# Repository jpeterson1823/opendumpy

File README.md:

# OpenDumpy: GB/C Dumping Tool

OpenDumpy is an open-source Gameboy and Gameboy Color cartridge dumper.

Planned Features:
- LCD Display Screen
- MicroSD Card Support
- Capacitive Touch Controls
- ROM Dump
  - Save direct to computer over USB via use of software
  - Save to MicroSD card through on-board UI
- SRAM Dump
  - Save direct to computer over USB via use of software
  - Save to MicroSD card through on-board UI
- SRAM Uploading from file
  - Direct from computer over USB via use of software
  - Load from MicroSD card through on-board UI
- Lots of docs!

Future versions of OpenDumpy will have a modular cartridge port to support NES, SNES, N64, as well as GB(A) games.

## Current Fabrication Status Status

OpenDumpy v3 has finished design and is being checked thoroughly for any design errors.
Ordering of components and PCBs will be completed early September 2026.

OpenDumpy v3 will include development pinouts accessible via IDC connectors on the right side of the board in the event of an uncaught error in PCB/Schematic design. This will allow for the continued development of firmware without needing to have a fixed board this time around.

## Setup & Building the UF2

### Install Required Packages

For Arch Linux:
- `cmake`
- `python`
- `base-devel`
- `arm-none-eabi-gcc`
- `arm-none-eabi-newlib`
- `arm-none-eabi-binutils`

For apt-based systems:
- `cmake`
- `python3`
- `build-essential`
- `gcc-arm-none-eabi`
- `libnewlib-arm-none-eabi`
- `libstdc++-arm-none-eabi-newlib`

### Cloning the Repo

When cloning this repo, make sure to _recursively_ initialize all submodules:

```
git clone https://github.com/jpeterson1823/opendumpy.git
cd opendumpy
git submodule update --init --recursive
```

### Compiling the Firmware

Assuming all package dependencies have been installed, building should be completed with CMake and Make.

It is recommended to create a build folder as to not muddy up the file tree:

```
mkdir firmware/build
cd firmware/build
cmake ..
make -j4
```

### Uploading the Firmware

Press the BOOTSEL button on OpenDumpy, then plug into USB port of machine. It will mount as a USB drive. Upload the built `opendumpy.uf2` file to the mounted drive. Voila!

## Images

### OpenDumpy v3
<div>

</div>

### OpenDumpy v1-2
<div>

</div>

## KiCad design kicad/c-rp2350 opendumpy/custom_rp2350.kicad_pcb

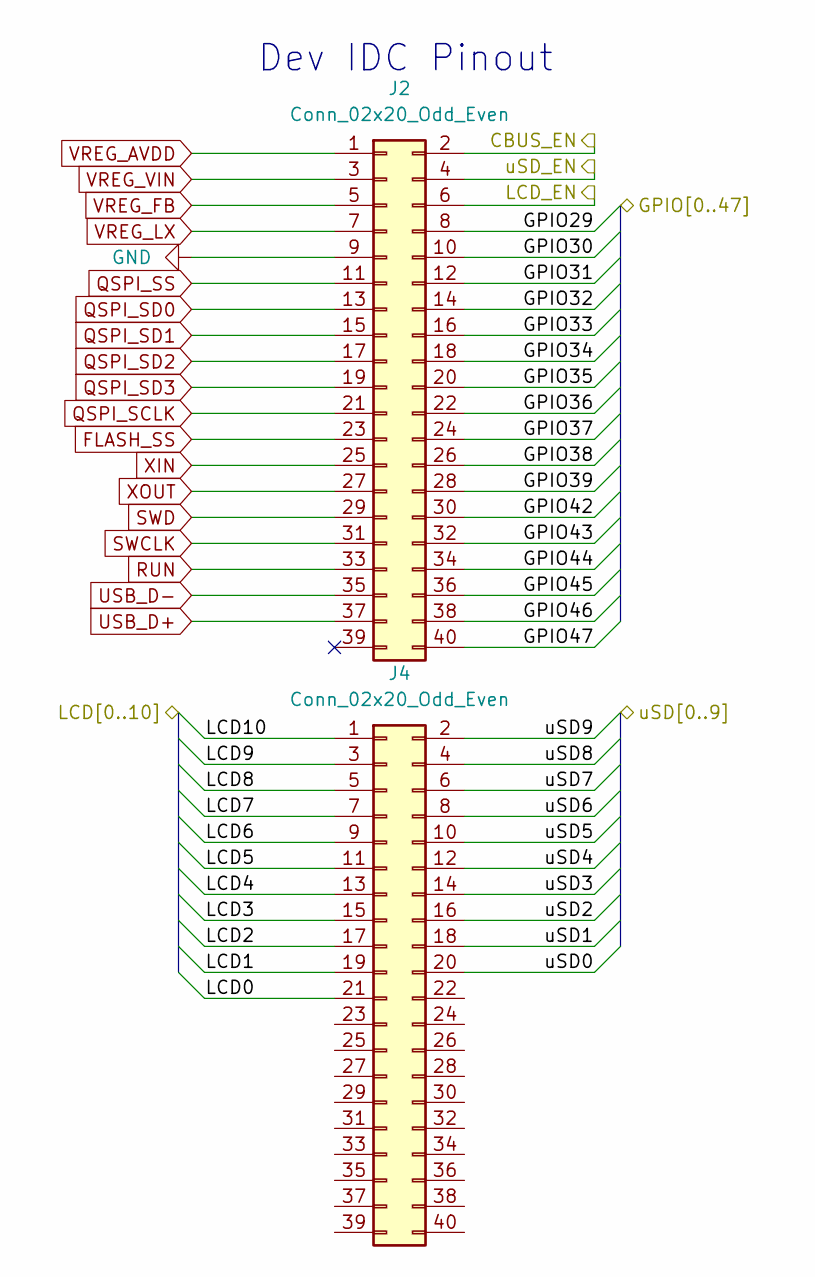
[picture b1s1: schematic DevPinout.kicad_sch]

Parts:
J2, J4: Conn_02x20_Odd_Even; Molex_8783240xx_2x20_P2.0mm_Header_Vertical_Polarized

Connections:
/DevPinout/CBUS_EN: J2.2; also elsewhere on the board
/DevPinout/LCD0: J4.21; also elsewhere on the board
/DevPinout/LCD1: J4.19; also elsewhere on the board
/DevPinout/LCD2: J4.17; also elsewhere on the board
/DevPinout/LCD3: J4.15; also elsewhere on the board
/DevPinout/LCD4: J4.13; also elsewhere on the board
/DevPinout/LCD5: J4.11; also elsewhere on the board
/DevPinout/LCD6: J4.9; also elsewhere on the board
/DevPinout/LCD7: J4.7; also elsewhere on the board
/DevPinout/LCD8: J4.5; also elsewhere on the board
/DevPinout/LCD9: J4.3; also elsewhere on the board
/DevPinout/LCD10: J4.1; also elsewhere on the board
/DevPinout/LCD_EN: J2.6; also elsewhere on the board
/DevPinout/uSD0: J4.20; also elsewhere on the board
/DevPinout/uSD1: J4.18; also elsewhere on the board
/DevPinout/uSD2: J4.16; also elsewhere on the board
/DevPinout/uSD3: J4.14; also elsewhere on the board
/DevPinout/uSD4: J4.12; also elsewhere on the board
/DevPinout/uSD5: J4.10; also elsewhere on the board
/DevPinout/uSD6: J4.8; also elsewhere on the board
/DevPinout/uSD7: J4.6; also elsewhere on the board
/DevPinout/uSD8: J4.4; also elsewhere on the board
/DevPinout/uSD9: J4.2; also elsewhere on the board
/DevPinout/uSD_EN: J2.4; also elsewhere on the board
/GPIO29: J2.8; also elsewhere on the board
/GPIO30: J2.10; also elsewhere on the board
/GPIO31: J2.12; also elsewhere on the board
/GPIO32: J2.14; also elsewhere on the board
/GPIO33: J2.16; also elsewhere on the board
/GPIO34: J2.18; also elsewhere on the board
/GPIO35: J2.20; also elsewhere on the board
/GPIO36: J2.22; also elsewhere on the board
/GPIO37: J2.24; also elsewhere on the board
/GPIO38: J2.26; also elsewhere on the board
/GPIO39: J2.28; also elsewhere on the board
/GPIO42: J2.30; also elsewhere on the board
/GPIO43: J2.32; also elsewhere on the board
/GPIO44: J2.34; also elsewhere on the board
/GPIO45: J2.36; also elsewhere on the board
/GPIO46: J2.38; also elsewhere on the board
/GPIO47: J2.40; also elsewhere on the board
FLASH_SS: J2.23; also elsewhere on the board
GND: J2.9; also elsewhere on the board
QSPI_SCLK: J2.21; also elsewhere on the board
QSPI_SD0: J2.13; also elsewhere on the board
QSPI_SD1: J2.15; also elsewhere on the board
QSPI_SD2: J2.17; also elsewhere on the board
QSPI_SD3: J2.19; also elsewhere on the board
QSPI_SS: J2.11; also elsewhere on the board
RUN: J2.33; also elsewhere on the board
SWCLK: J2.31; also elsewhere on the board
SWD: J2.29; also elsewhere on the board
USB_D+: J2.37; also elsewhere on the board
USB_D-: J2.35; also elsewhere on the board
VREG_AVDD: J2.1; also elsewhere on the board
VREG_FB: J2.5; also elsewhere on the board
VREG_LX: J2.7; also elsewhere on the board
VREG_VIN: J2.3; also elsewhere on the board
XIN: J2.25; also elsewhere on the board
XOUT: J2.27; also elsewhere on the board

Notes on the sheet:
Dev IDC Pinout

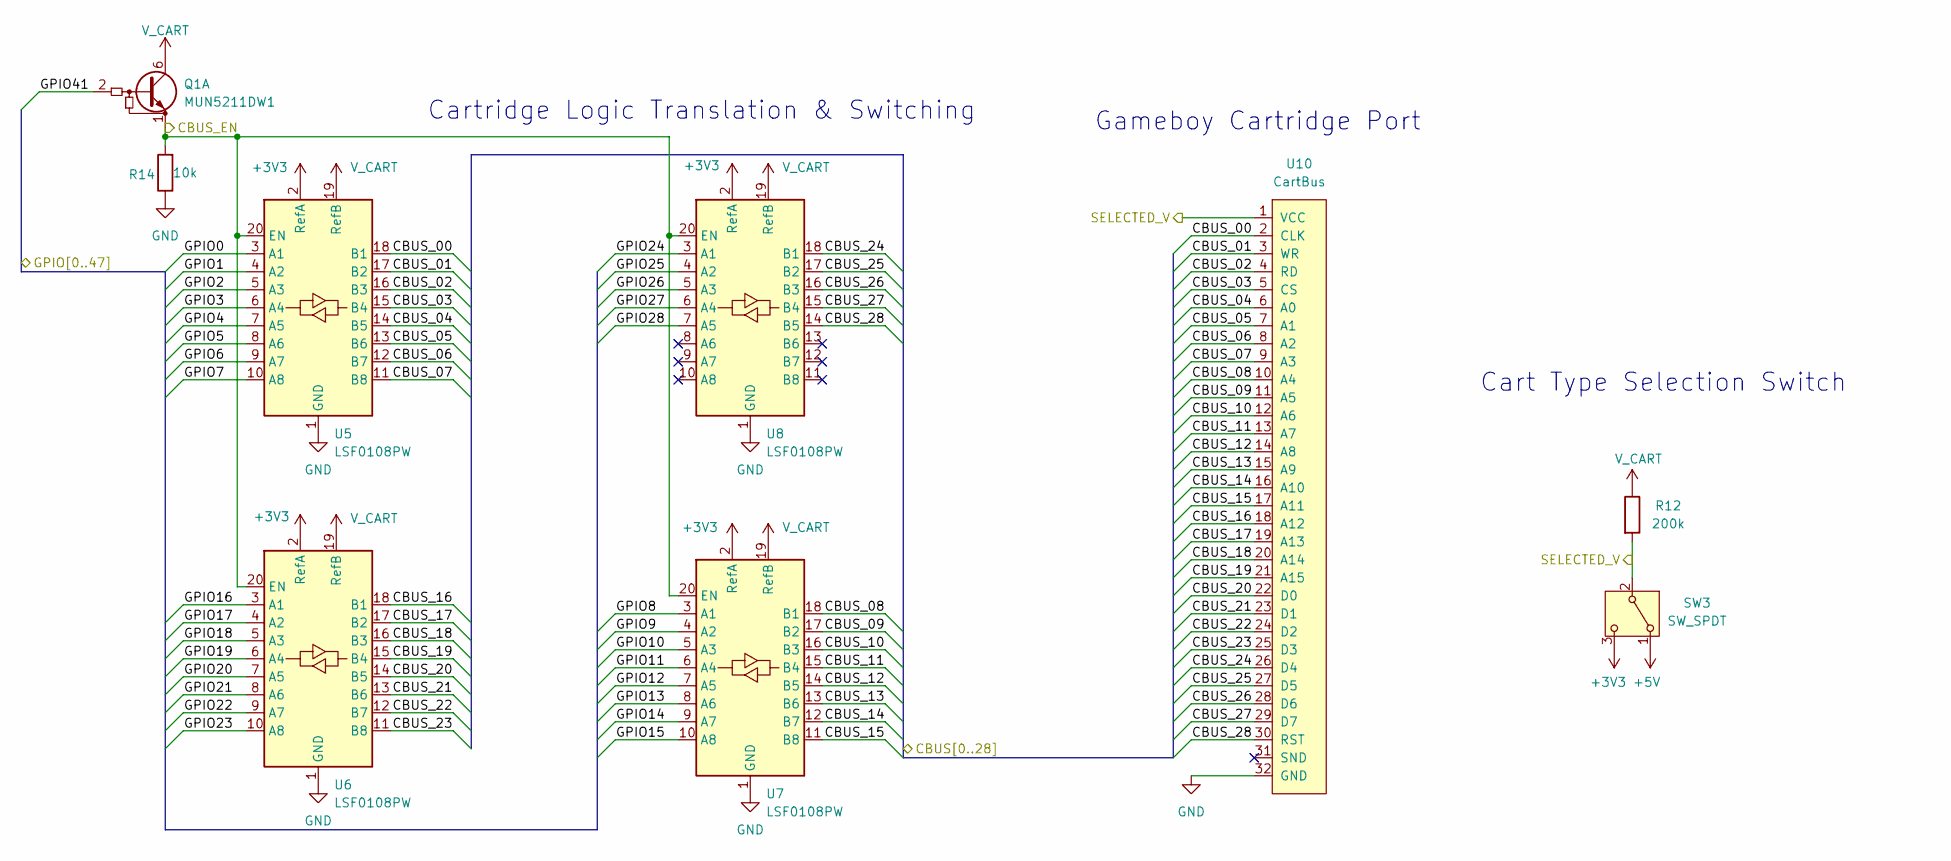
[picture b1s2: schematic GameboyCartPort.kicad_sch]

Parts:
Q1: MUN5211DW1; SOT-363_SC-70-6
R12: 200k; R_01005_0402Metric
R14: 10k; R_0402_1005Metric_Pad0.72x0.64mm_HandSolder
SW3: SW_SPDT; CL-SB-12B-01_NDC
U5, U6, U7, U8: LSF0108PW; TSSOP-20_4.4x6.5mm_P0.65mm
U10: CartBus; DSL_Cartridge_Reader

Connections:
+5V: SW3.1 (A); also elsewhere on the board
/DevPinout/CBUS_EN: Q1.1 (E1), R14.2, U5.20 (EN), U6.20 (EN), U7.20 (EN), U8.20 (EN); also elsewhere on the board
/GPIO0: U5.3 (A1); also elsewhere on the board
/GPIO1: U5.4 (A2); also elsewhere on the board
/GPIO2: U5.5 (A3); also elsewhere on the board
/GPIO3: U5.6 (A4); also elsewhere on the board
/GPIO4: U5.7 (A5); also elsewhere on the board
/GPIO5: U5.8 (A6); also elsewhere on the board
/GPIO6: U5.9 (A7); also elsewhere on the board
/GPIO7: U5.10 (A8); also elsewhere on the board
/GPIO8: U7.3 (A1); also elsewhere on the board
/GPIO9: U7.4 (A2); also elsewhere on the board
/GPIO10: U7.5 (A3); also elsewhere on the board
/GPIO11: U7.6 (A4); also elsewhere on the board
/GPIO12: U7.7 (A5); also elsewhere on the board
/GPIO13: U7.8 (A6); also elsewhere on the board
/GPIO14: U7.9 (A7); also elsewhere on the board
/GPIO15: U7.10 (A8); also elsewhere on the board
/GPIO16: U6.3 (A1); also elsewhere on the board
/GPIO17: U6.4 (A2); also elsewhere on the board
/GPIO18: U6.5 (A3); also elsewhere on the board
/GPIO19: U6.6 (A4); also elsewhere on the board
/GPIO20: U6.7 (A5); also elsewhere on the board
/GPIO21: U6.8 (A6); also elsewhere on the board
/GPIO22: U6.9 (A7); also elsewhere on the board
/GPIO23: U6.10 (A8); also elsewhere on the board
/GPIO24: U8.3 (A1); also elsewhere on the board
/GPIO25: U8.4 (A2); also elsewhere on the board
/GPIO26: U8.5 (A3); also elsewhere on the board
/GPIO27: U8.6 (A4); also elsewhere on the board
/GPIO28: U8.7 (A5); also elsewhere on the board
/GPIO41: Q1.2 (B1); also elsewhere on the board
/GameboyCartPort/CBUS_00: U5.18 (B1), U10.2 (CLK~)
/GameboyCartPort/CBUS_01: U5.17 (B2), U10.3 (WR)
/GameboyCartPort/CBUS_02: U5.16 (B3), U10.4 (RD)
/GameboyCartPort/CBUS_03: U5.15 (B4), U10.5 (CS)
/GameboyCartPort/CBUS_04: U5.14 (B5), U10.6 (A0)
/GameboyCartPort/CBUS_05: U5.13 (B6), U10.7 (A1)
/GameboyCartPort/CBUS_06: U5.12 (B7), U10.8 (A2)
/GameboyCartPort/CBUS_07: U5.11 (B8), U10.9 (A3)
/GameboyCartPort/CBUS_08: U7.18 (B1), U10.10 (A4)
/GameboyCartPort/CBUS_09: U7.17 (B2), U10.11 (A5)
/GameboyCartPort/CBUS_10: U7.16 (B3), U10.12 (A6)
/GameboyCartPort/CBUS_11: U7.15 (B4), U10.13 (A7)
/GameboyCartPort/CBUS_12: U7.14 (B5), U10.14 (A8)
/GameboyCartPort/CBUS_13: U7.13 (B6), U10.15 (A9)
/GameboyCartPort/CBUS_14: U7.12 (B7), U10.16 (A10)
/GameboyCartPort/CBUS_15: U7.11 (B8), U10.17 (A11)
/GameboyCartPort/CBUS_16: U6.18 (B1), U10.18 (A12)
/GameboyCartPort/CBUS_17: U6.17 (B2), U10.19 (A13)
/GameboyCartPort/CBUS_18: U6.16 (B3), U10.20 (A14)
/GameboyCartPort/CBUS_19: U6.15 (B4), U10.21 (A15)
/GameboyCartPort/CBUS_20: U6.14 (B5), U10.22 (D0)
/GameboyCartPort/CBUS_21: U6.13 (B6), U10.23 (D1)
/GameboyCartPort/CBUS_22: U6.12 (B7), U10.24 (D2)
/GameboyCartPort/CBUS_23: U6.11 (B8), U10.25 (D3)
/GameboyCartPort/CBUS_24: U8.18 (B1), U10.26 (D4)
/GameboyCartPort/CBUS_25: U8.17 (B2), U10.27 (D5)
/GameboyCartPort/CBUS_26: U8.16 (B3), U10.28 (D6)
/GameboyCartPort/CBUS_27: U8.15 (B4), U10.29 (D7)
/GameboyCartPort/CBUS_28: U8.14 (B5), U10.30 (RST)
/GameboyCartPort/SELECTED_V: R12.2, SW3.2 (B), U10.1 (VCC)
GND: R14.1, U5.1 (GND), U6.1 (GND), U7.1 (GND), U8.1 (GND), U10.32 (GND); also elsewhere on the board
VREG_VIN: SW3.3 (C), U5.2 (RefA), U6.2 (RefA), U7.2 (RefA), U8.2 (RefA); also elsewhere on the board
V_CART: Q1.6 (C1), R12.1, U5.19 (RefB), U6.19 (RefB), U7.19 (RefB), U8.19 (RefB)

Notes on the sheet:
Cartridge Logic Translation & Switching
Cart Type Selection Switch
Gameboy Cartridge Port

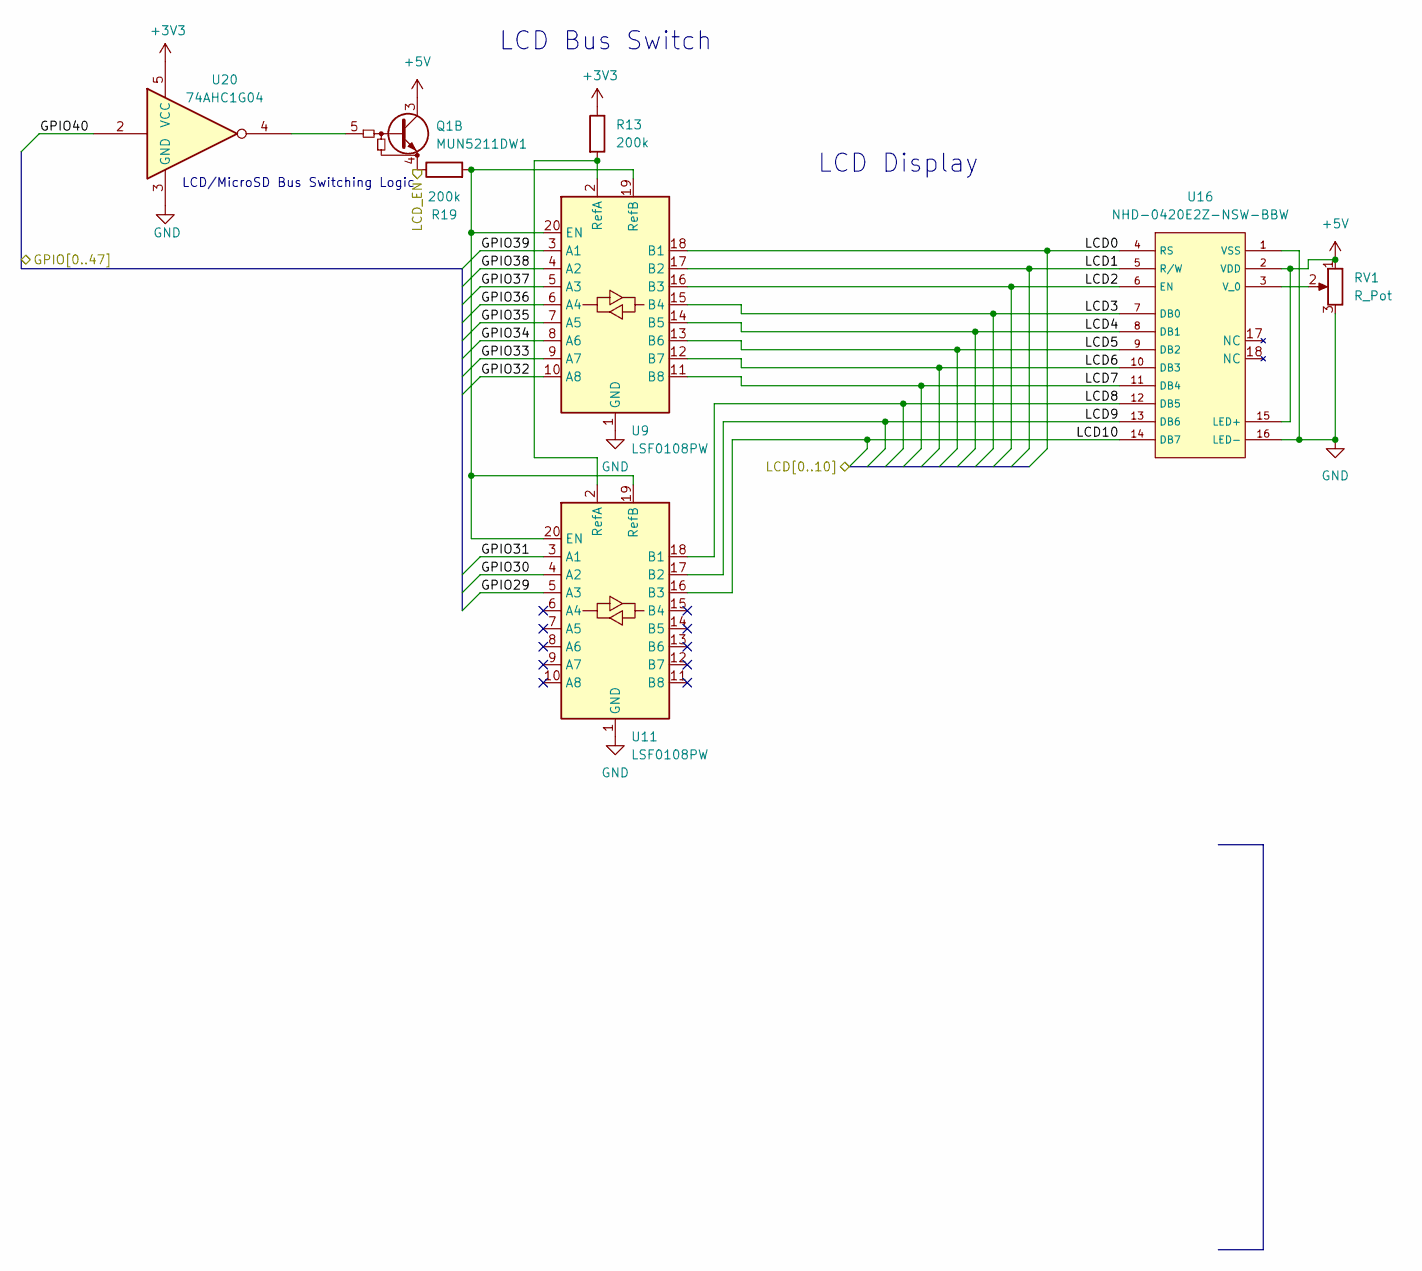
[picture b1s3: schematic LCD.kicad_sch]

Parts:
Q1: MUN5211DW1; SOT-363_SC-70-6
R13, R19: 200k; R_01005_0402Metric
RV1: R_Pot; Potentiometer_Bourns_TC33X_Vertical
U9, U11: LSF0108PW; TSSOP-20_4.4x6.5mm_P0.65mm
U16: NHD-0420E2Z-NSW-BBW
U20: 74AHC1G04; SOT-353_SC-70-5

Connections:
+5V: Q1.3 (C2), RV1.1, U16.2 (VDD), U16.15 (LED+); also elsewhere on the board
/DevPinout/LCD0: U9.18 (B1), U16.4 (RS); also elsewhere on the board
/DevPinout/LCD1: U9.17 (B2), U16.5 (R/W); also elsewhere on the board
/DevPinout/LCD2: U9.16 (B3), U16.6 (EN); also elsewhere on the board
/DevPinout/LCD3: U9.15 (B4), U16.7 (DB0); also elsewhere on the board
/DevPinout/LCD4: U9.14 (B5), U16.8 (DB1); also elsewhere on the board
/DevPinout/LCD5: U9.13 (B6), U16.9 (DB2); also elsewhere on the board
/DevPinout/LCD6: U9.12 (B7), U16.10 (DB3); also elsewhere on the board
/DevPinout/LCD7: U9.11 (B8), U16.11 (DB4); also elsewhere on the board
/DevPinout/LCD8: U11.18 (B1), U16.12 (DB5); also elsewhere on the board
/DevPinout/LCD9: U11.17 (B2), U16.13 (DB6); also elsewhere on the board
/DevPinout/LCD10: U11.16 (B3), U16.14 (DB7); also elsewhere on the board
/DevPinout/LCD_EN: Q1.4 (E2), R19.1; also elsewhere on the board
/GPIO29: U11.5 (A3); also elsewhere on the board
/GPIO30: U11.4 (A2); also elsewhere on the board
/GPIO31: U11.3 (A1); also elsewhere on the board
/GPIO32: U9.10 (A8); also elsewhere on the board
/GPIO33: U9.9 (A7); also elsewhere on the board
/GPIO34: U9.8 (A6); also elsewhere on the board
/GPIO35: U9.7 (A5); also elsewhere on the board
/GPIO36: U9.6 (A4); also elsewhere on the board
/GPIO37: U9.5 (A3); also elsewhere on the board
/GPIO38: U9.4 (A2); also elsewhere on the board
/GPIO39: U9.3 (A1); also elsewhere on the board
/GPIO40: U20.2; also elsewhere on the board
GND: RV1.3, U9.1 (GND), U11.1 (GND), U16.1 (VSS), U16.16 (LED-), U20.3 (GND); also elsewhere on the board
unnamed: Q1.5 (B2), U20.4
unnamed: R19.2, U9.19 (RefB), U9.20 (EN), U11.19 (RefB), U11.20 (EN)
unnamed: R13.2, U9.2 (RefA), U11.2 (RefA)
unnamed: RV1.2, U16.3 (V_0)
VREG_VIN: R13.1, U20.5 (VCC); also elsewhere on the board

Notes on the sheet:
LCD/MicroSD Bus Switching Logic
LCD Display
LCD Bus Switch

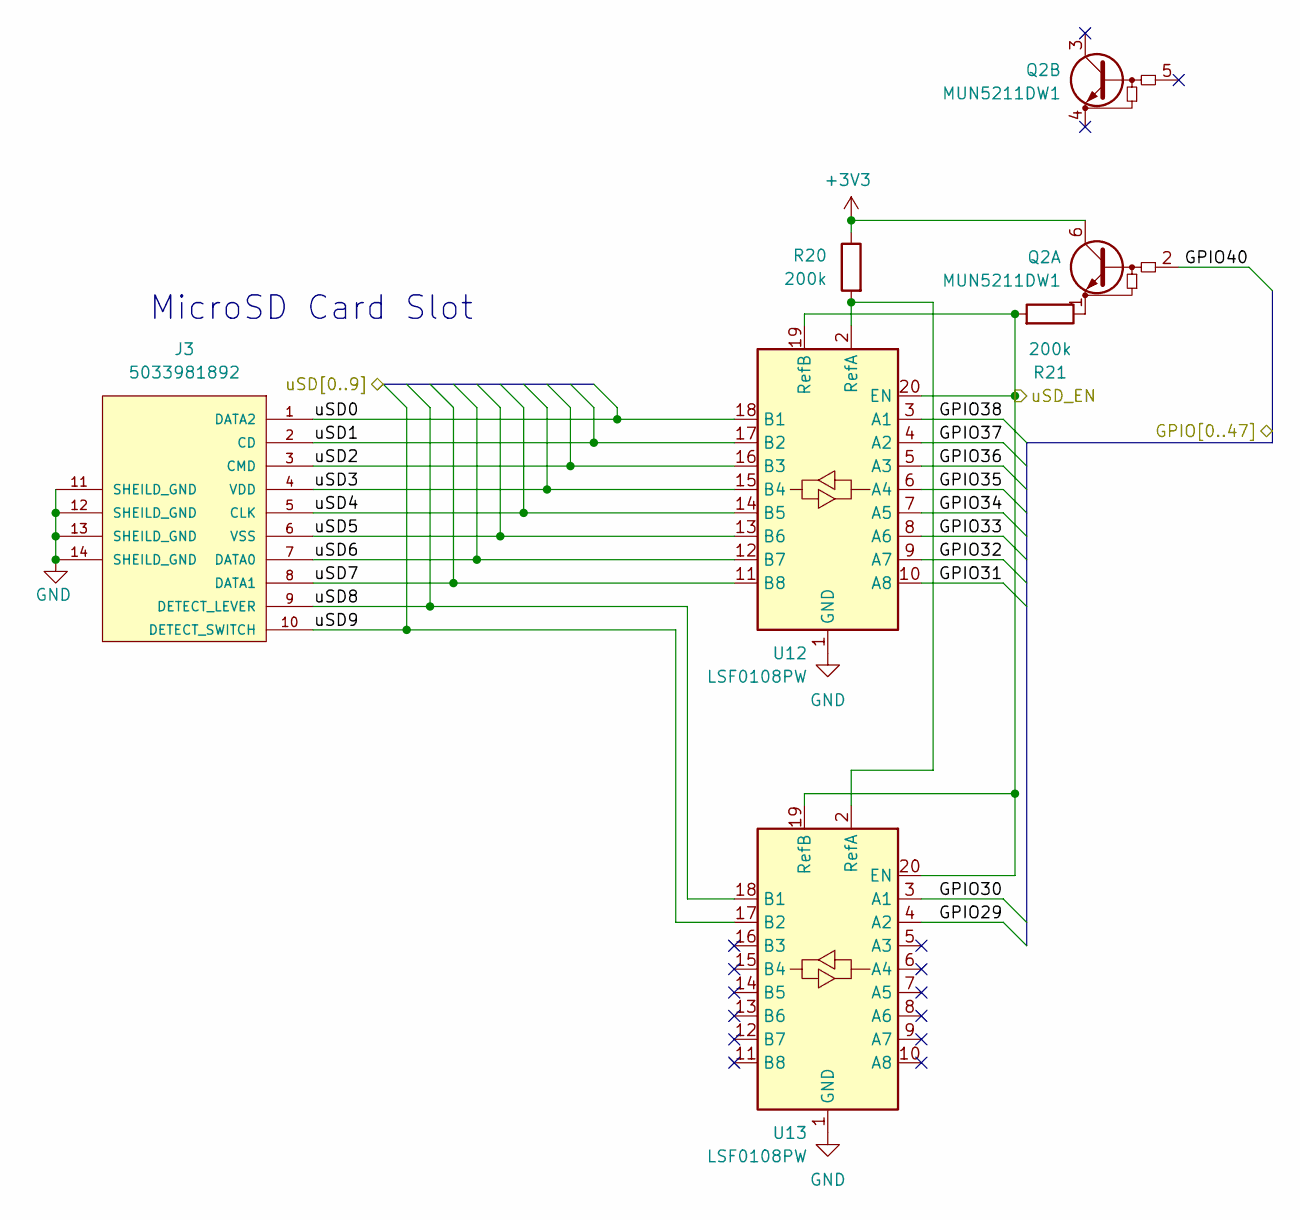
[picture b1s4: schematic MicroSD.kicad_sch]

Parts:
J3: 5033981892; CONN_503398-1892_MOL; MANUFACTURER_PART_NUMBER 5033981892; DigiKey_Part_Number WM11190CT-ND
Q2: MUN5211DW1; SOT-363_SC-70-6
R20, R21: 200k; R_01005_0402Metric
U12, U13: LSF0108PW; TSSOP-20_4.4x6.5mm_P0.65mm

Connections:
/DevPinout/uSD0: J3.1 (DATA2), U12.18 (B1); also elsewhere on the board
/DevPinout/uSD1: J3.2 (CD), U12.17 (B2); also elsewhere on the board
/DevPinout/uSD2: J3.3 (CMD), U12.16 (B3); also elsewhere on the board
/DevPinout/uSD3: J3.4 (VDD), U12.15 (B4); also elsewhere on the board
/DevPinout/uSD4: J3.5 (CLK), U12.14 (B5); also elsewhere on the board
/DevPinout/uSD5: J3.6 (VSS), U12.13 (B6); also elsewhere on the board
/DevPinout/uSD6: J3.7 (DATA0), U12.12 (B7); also elsewhere on the board
/DevPinout/uSD7: J3.8 (DATA1), U12.11 (B8); also elsewhere on the board
/DevPinout/uSD8: J3.9 (DETECT_LEVER), U13.18 (B1); also elsewhere on the board
/DevPinout/uSD9: J3.10 (DETECT_SWITCH), U13.17 (B2); also elsewhere on the board
/DevPinout/uSD_EN: R21.2, U12.19 (RefB), U12.20 (EN), U13.19 (RefB), U13.20 (EN); also elsewhere on the board
/GPIO29: U13.4 (A2); also elsewhere on the board
/GPIO30: U13.3 (A1); also elsewhere on the board
/GPIO31: U12.10 (A8); also elsewhere on the board
/GPIO32: U12.9 (A7); also elsewhere on the board
/GPIO33: U12.8 (A6); also elsewhere on the board
/GPIO34: U12.7 (A5); also elsewhere on the board
/GPIO35: U12.6 (A4); also elsewhere on the board
/GPIO36: U12.5 (A3); also elsewhere on the board
/GPIO37: U12.4 (A2); also elsewhere on the board
/GPIO38: U12.3 (A1); also elsewhere on the board
/GPIO40: Q2.2 (B1); also elsewhere on the board
GND: J3.11 (SHEILD_GND), J3.12 (SHEILD_GND), J3.13 (SHEILD_GND), J3.14 (SHEILD_GND), U12.1 (GND), U13.1 (GND); also elsewhere on the board
unnamed: Q2.1 (E1), R21.1
unnamed: R20.2, U12.2 (RefA), U13.2 (RefA)
VREG_VIN: Q2.6 (C1), R20.1; also elsewhere on the board

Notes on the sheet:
MicroSD Card Slot

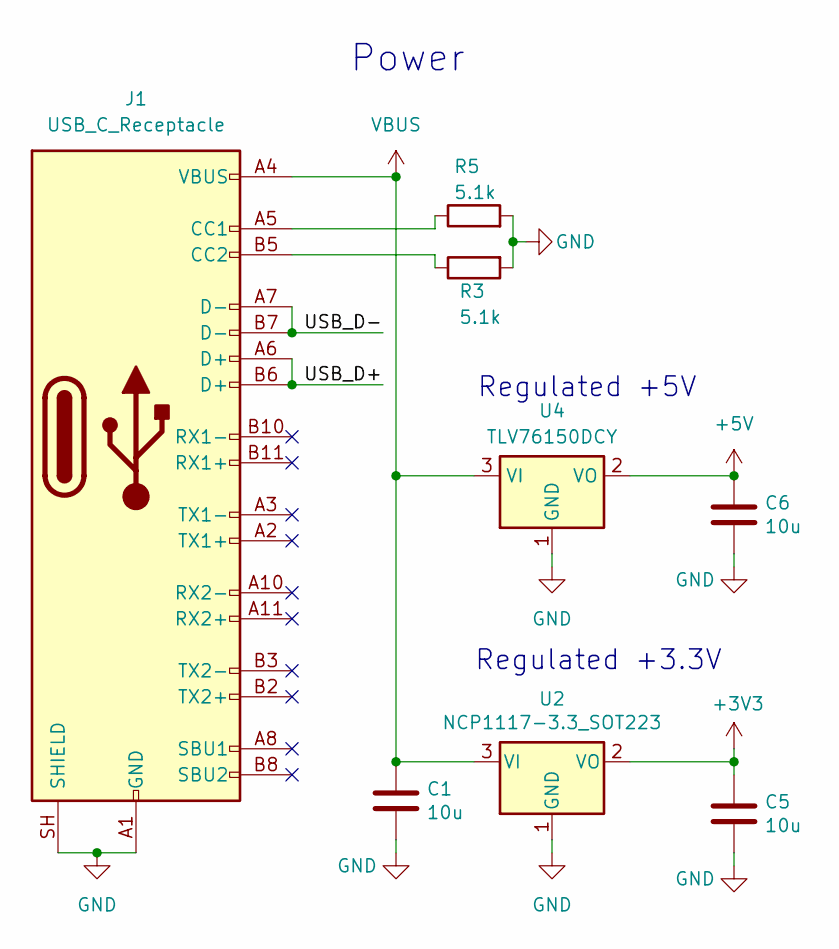
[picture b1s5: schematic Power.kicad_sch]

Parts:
C1, C5, C6: 10u; C_0402_1005Metric
J1: USB_C_Receptacle; USB_C_Receptacle_Amphenol_12401610E4-2A
R3, R5: 5.1k; R_0402_1005Metric
U2: NCP1117-3.3_SOT223; SOT-223-3_TabPin2
U4: TLV76150DCY; SOT-223-3_TabPin2

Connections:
+5V: C6.1, U4.2 (VO); also elsewhere on the board
GND: C1.2, C5.2, C6.2, J1.A1 (GND), J1.A12 (GND), J1.B1 (GND), J1.B12 (GND), J1.SH (SHIELD), R3.2, R5.2, U2.1 (GND), U4.1 (GND); also elsewhere on the board
unnamed: J1.A5 (CC1), R5.1
unnamed: J1.B5 (CC2), R3.1
USB_D+: J1.A6 (D+), J1.B6 (D+); also elsewhere on the board
USB_D-: J1.A7 (D-), J1.B7 (D-); also elsewhere on the board
VBUS: C1.1, J1.A4 (VBUS), J1.A9 (VBUS), J1.B4 (VBUS), J1.B9 (VBUS), U2.3 (VI), U4.3 (VI)
VREG_VIN: C5.1, U2.2 (VO); also elsewhere on the board

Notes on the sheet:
Power
Regulated +3.3V
Regulated +5V

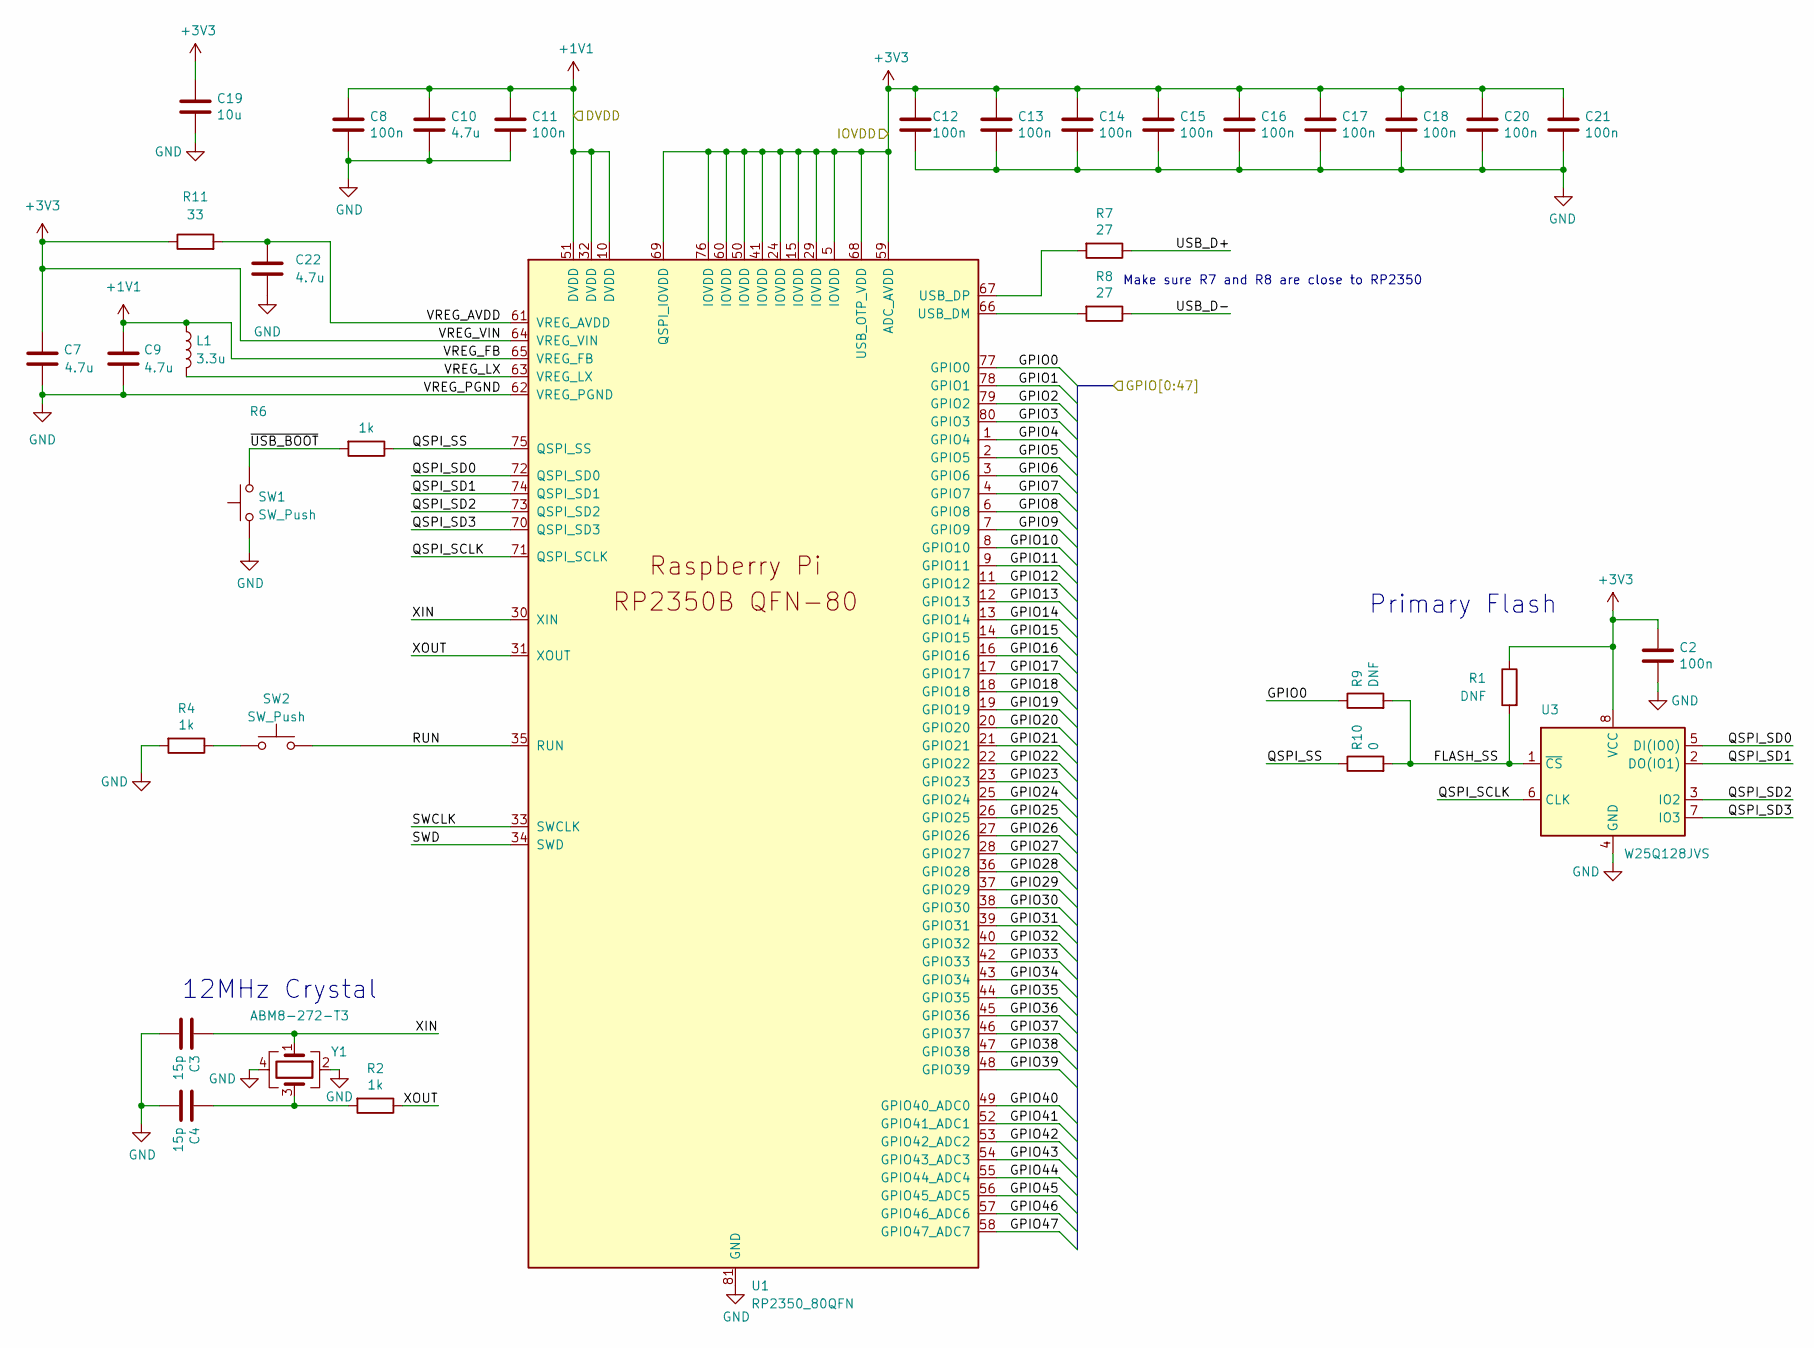
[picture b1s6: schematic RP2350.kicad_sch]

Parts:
C2, C8, C11, C12, C13, C14, C15, C16, C17, C18, C20, C21: 100n; C_0402_1005Metric
C3, C4: 15p; C_0402_1005Metric
C7, C9, C10, C22: 4.7u; C_0402_1005Metric
C19: 10u; C_0402_1005Metric
L1: 3.3u; L_01005_0402Metric
R1, R9: DNF; R_0402_1005Metric
R2, R4, R6: 1k; R_0402_1005Metric
R7, R8: 27; R_0402_1005Metric
R10: 0; R_0402_1005Metric
R11: 33; R_0402_1005Metric
SW1, SW2: SW_Push; SW_Push_1P1T_NO_Vertical_Wuerth_434133025816
U1: RP2350_80QFN; QFN-80-1EP_10x10mm_P0.4mm_EP3.4x3.4mm
U3: W25Q128JVS; SOIC-8_5.3x5.3mm_P1.27mm
Y1: ABM8-272-T3; Crystal_SMD_3225-4Pin_3.2x2.5mm

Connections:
/GPIO0: R9.1, U1.77 (GPIO0); also elsewhere on the board
/GPIO1: U1.78 (GPIO1); also elsewhere on the board
/GPIO2: U1.79 (GPIO2); also elsewhere on the board
/GPIO3: U1.80 (GPIO3); also elsewhere on the board
/GPIO4: U1.1 (GPIO4); also elsewhere on the board
/GPIO5: U1.2 (GPIO5); also elsewhere on the board
/GPIO6: U1.3 (GPIO6); also elsewhere on the board
/GPIO7: U1.4 (GPIO7); also elsewhere on the board
/GPIO8: U1.6 (GPIO8); also elsewhere on the board
/GPIO9: U1.7 (GPIO9); also elsewhere on the board
/GPIO10: U1.8 (GPIO10); also elsewhere on the board
/GPIO11: U1.9 (GPIO11); also elsewhere on the board
/GPIO12: U1.11 (GPIO12); also elsewhere on the board
/GPIO13: U1.12 (GPIO13); also elsewhere on the board
/GPIO14: U1.13 (GPIO14); also elsewhere on the board
/GPIO15: U1.14 (GPIO15); also elsewhere on the board
/GPIO16: U1.16 (GPIO16); also elsewhere on the board
/GPIO17: U1.17 (GPIO17); also elsewhere on the board
/GPIO18: U1.18 (GPIO18); also elsewhere on the board
/GPIO19: U1.19 (GPIO19); also elsewhere on the board
/GPIO20: U1.20 (GPIO20); also elsewhere on the board
/GPIO21: U1.21 (GPIO21); also elsewhere on the board
/GPIO22: U1.22 (GPIO22); also elsewhere on the board
/GPIO23: U1.23 (GPIO23); also elsewhere on the board
/GPIO24: U1.25 (GPIO24); also elsewhere on the board
/GPIO25: U1.26 (GPIO25); also elsewhere on the board
/GPIO26: U1.27 (GPIO26); also elsewhere on the board
/GPIO27: U1.28 (GPIO27); also elsewhere on the board
/GPIO28: U1.36 (GPIO28); also elsewhere on the board
/GPIO29: U1.37 (GPIO29); also elsewhere on the board
/GPIO30: U1.38 (GPIO30); also elsewhere on the board
/GPIO31: U1.39 (GPIO31); also elsewhere on the board
/GPIO32: U1.40 (GPIO32); also elsewhere on the board
/GPIO33: U1.42 (GPIO33); also elsewhere on the board
/GPIO34: U1.43 (GPIO34); also elsewhere on the board
/GPIO35: U1.44 (GPIO35); also elsewhere on the board
/GPIO36: U1.45 (GPIO36); also elsewhere on the board
/GPIO37: U1.46 (GPIO37); also elsewhere on the board
/GPIO38: U1.47 (GPIO38); also elsewhere on the board
/GPIO39: U1.48 (GPIO39); also elsewhere on the board
/GPIO40: U1.49 (GPIO40_ADC0); also elsewhere on the board
/GPIO41: U1.52 (GPIO41_ADC1); also elsewhere on the board
/GPIO42: U1.53 (GPIO42_ADC2); also elsewhere on the board
/GPIO43: U1.54 (GPIO43_ADC3); also elsewhere on the board
/GPIO44: U1.55 (GPIO44_ADC4); also elsewhere on the board
/GPIO45: U1.56 (GPIO45_ADC5); also elsewhere on the board
/GPIO46: U1.57 (GPIO46_ADC6); also elsewhere on the board
/GPIO47: U1.58 (GPIO47_ADC7); also elsewhere on the board
FLASH_SS: R1.2, R9.2, R10.2, U3.1 (~CS); also elsewhere on the board
GND: C2.2, C3.2, C4.2, C7.2, C8.2, C9.2, C10.2, C11.2, C12.2, C13.2, C14.2, C15.2, C16.2, C17.2, C18.2, C19.2, C20.2, C21.2, C22.1, R4.2, SW1.1, U1.62 (VREG_PGND), U1.81 (GND), U3.4 (GND), Y1.2, Y1.4; also elsewhere on the board
unnamed: C4.1, R2.2, Y1.3
unnamed: R4.1, SW2.1
unnamed: R8.2, U1.66 (USB_DM)
unnamed: R7.2, U1.67 (USB_DP)
QSPI_SCLK: U1.71 (QSPI_SCLK), U3.6 (CLK); also elsewhere on the board
QSPI_SD0: U1.72 (QSPI_SD0), U3.5 (DI(IO0)); also elsewhere on the board
QSPI_SD1: U1.74 (QSPI_SD1), U3.2 (DO(IO1)); also elsewhere on the board
QSPI_SD2: U1.73 (QSPI_SD2), U3.3 (IO2); also elsewhere on the board
QSPI_SD3: U1.70 (QSPI_SD3), U3.7 (IO3); also elsewhere on the board
QSPI_SS: R6.1, R10.1, U1.75 (QSPI_SS); also elsewhere on the board
RUN: SW2.2, U1.35 (RUN); also elsewhere on the board
SWCLK: U1.33 (SWCLK); also elsewhere on the board
SWD: U1.34 (SWD); also elsewhere on the board
USB_D+: R7.1; also elsewhere on the board
USB_D-: R8.1; also elsewhere on the board
VREG_AVDD: C22.2, R11.2, U1.61 (VREG_AVDD); also elsewhere on the board
VREG_FB: C8.1, C9.1, C10.1, C11.1, L1.1, U1.10 (DVDD), U1.32 (DVDD), U1.51 (DVDD), U1.65 (VREG_FB); also elsewhere on the board
VREG_LX: L1.2, U1.63 (VREG_LX); also elsewhere on the board
VREG_VIN: C2.1, C7.1, C12.1, C13.1, C14.1, C15.1, C16.1, C17.1, C18.1, C19.1, C20.1, C21.1, R1.1, R11.1, U1.5 (IOVDD), U1.15 (IOVDD), U1.24 (IOVDD), U1.29 (IOVDD), U1.41 (IOVDD), U1.50 (IOVDD), U1.59 (ADC_AVDD), U1.60 (IOVDD), U1.64 (VREG_VIN), U1.68 (USB_OTP_VDD), U1.69 (QSPI_IOVDD), U1.76 (IOVDD), U3.8 (VCC); also elsewhere on the board
XIN: C3.1, U1.30 (XIN), Y1.1; also elsewhere on the board
XOUT: R2.1, U1.31 (XOUT); also elsewhere on the board
~USB_BOOT: R6.2, SW1.2

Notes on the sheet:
12MHz Crystal
Primary Flash
Make sure R7 and R8 are close to RP2350

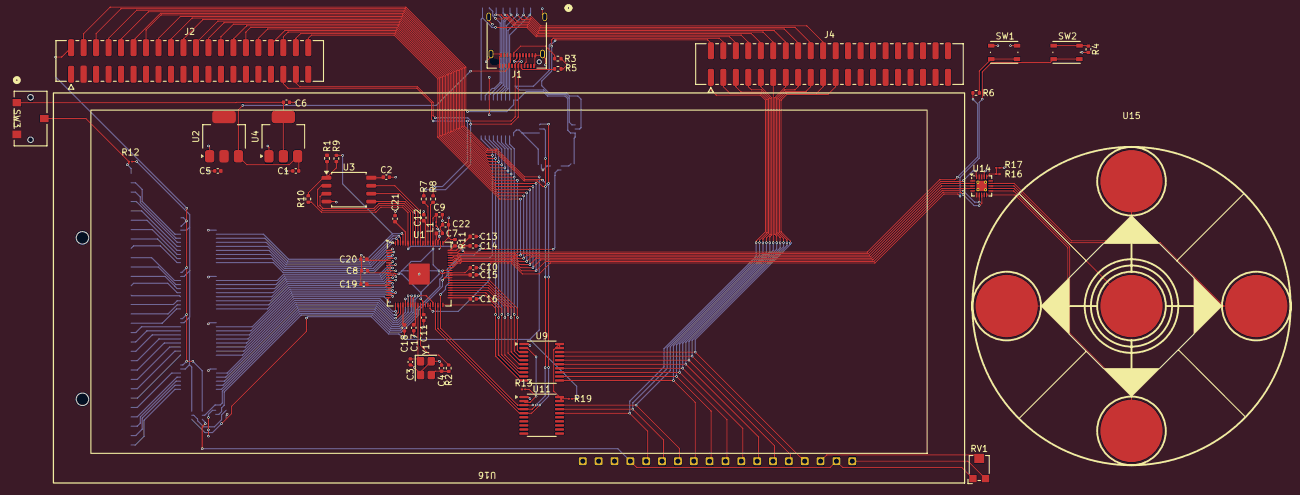
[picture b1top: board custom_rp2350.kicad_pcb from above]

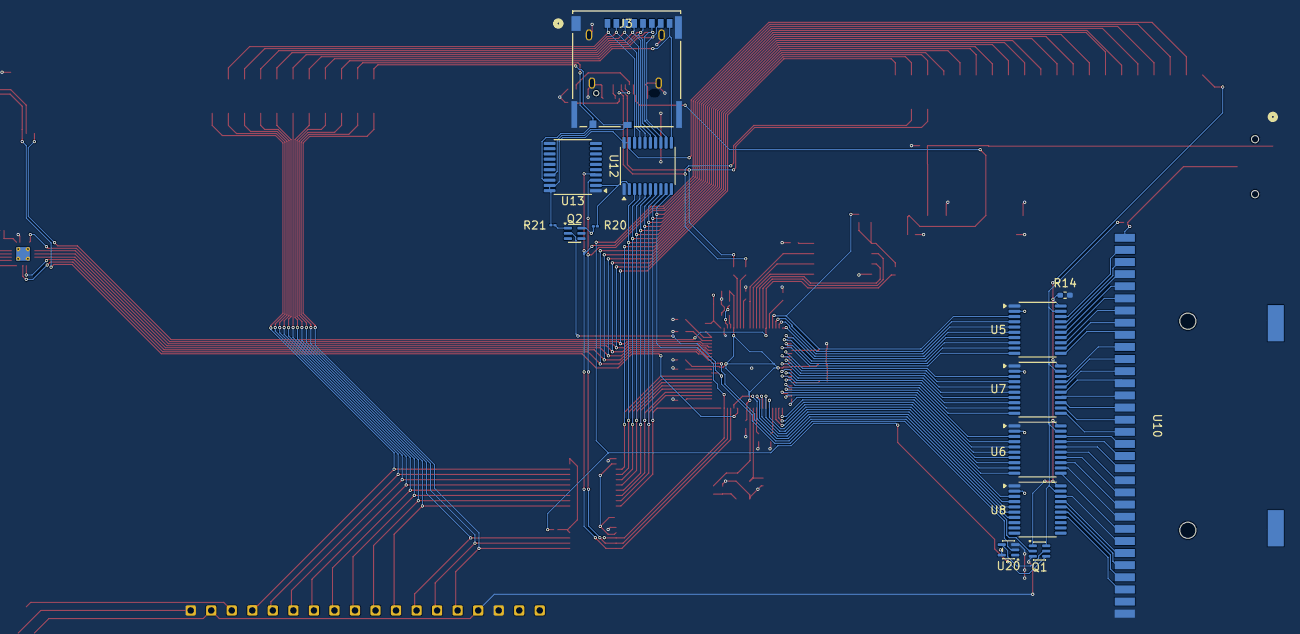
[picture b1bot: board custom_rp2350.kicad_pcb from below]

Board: 2 copper layers, 70 parts (14 on the bottom side), 141 nets.

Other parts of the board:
R16: 6.5k; R_01005_0402Metric
R17: 10k; R_01005_0402Metric
U14: MTCH1060T-I; VQFN-20-1EP_3x3mm_P0.4mm_EP1.7x1.7mm_ThermalVias
U15: TouchPad

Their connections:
/GPIO42: U14.8 (BTN_4); also elsewhere on the board
/GPIO43: U14.7 (BTN_3); also elsewhere on the board
/GPIO44: U14.4 (BTN_2); also elsewhere on the board
/GPIO45: U14.3 (BTN_1); also elsewhere on the board
/GPIO46: U14.2 (BTN_0); also elsewhere on the board
/GPIO47: U14.20 (CFG_2); also elsewhere on the board
GND: R17.2, U14.17 (VSS); also elsewhere on the board
unnamed: R16.2, R17.1, U14.16 (CFG_0)
unnamed: U14.10 (OUT_0), U15.2 (BTN_1)
unnamed: U14.11 (OUT_1), U15.3 (BTN_2)
unnamed: U14.12 (OUT_2), U15.5 (BTN_4)
VREG_VIN: R16.1, U14.1 (EASY_TUNE), U14.6 (SINGLE_BTN), U14.18 (VDD), U14.19 (CFG_1); also elsewhere on the board

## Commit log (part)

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2026-06-28 Pushing Current Progress
    Current PCB design that's on order with all current documentation
2026-06-28 Started README.md
2026-06-28 Uploading README imgs & Updated gitignore
2026-06-29 Updated README & Added SRC Template
2026-06-29 Created GB function skeleton
